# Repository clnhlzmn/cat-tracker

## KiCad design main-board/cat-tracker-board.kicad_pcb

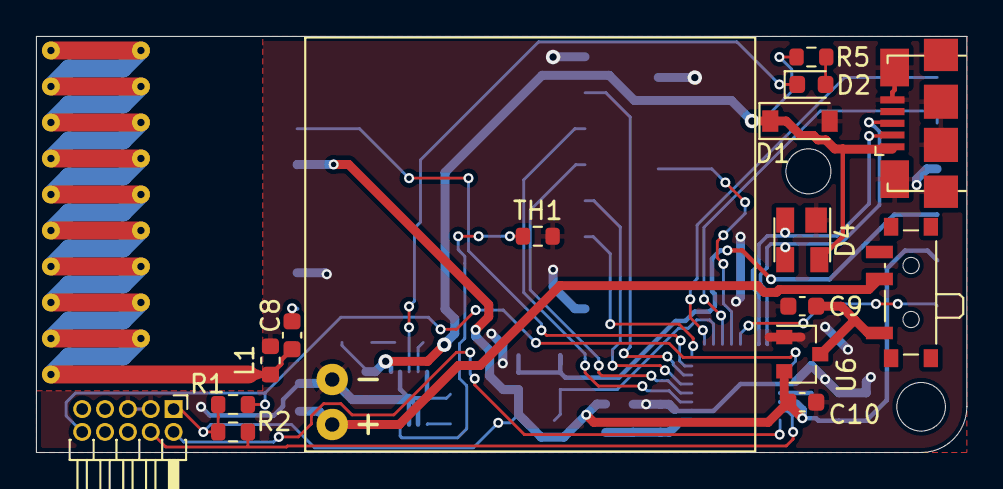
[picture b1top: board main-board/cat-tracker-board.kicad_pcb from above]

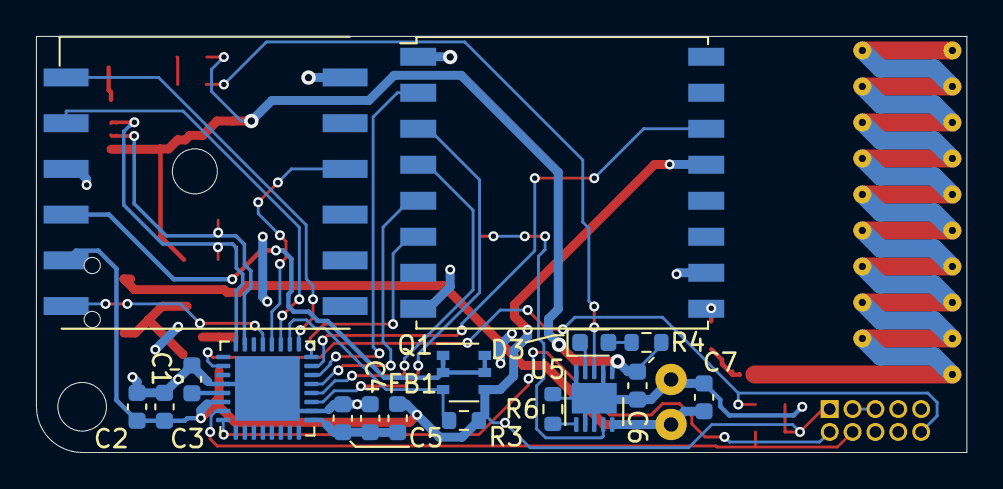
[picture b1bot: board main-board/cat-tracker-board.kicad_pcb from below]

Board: 2 copper layers, 51.7 x 23.1 mm, 34 parts (17 on the bottom side), 32 nets.

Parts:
AE1: Antenna; Texas_SWRA416_868MHz_915MHz
BT1: ASR00007; TinyCircuits_ASR00007
C1, C9, C10: 1 uF; C_0603_1608Metric
C2, C4: 10 uF; C_0603_1608Metric
C3, C5: 0.1 uF; C_0603_1608Metric
C6, C7: 4.7 uF; C_0603_1608Metric
C8: 1 pF; C_0603_1608Metric
D1: PTVS5V0S1UTR,115; D_SOD-123
D2, D3: LED; LED_0603_1608Metric
D4: PRTR5V0U2X; SOT-143
FB1: Ferrite_Bead; L_0603_1608Metric
J1: Conn_01x10; PinHeader_2x05_P1.27mm_Horizontal
J3: USB_B_Micro; USB_Micro-B_Amphenol_10118192_Horizontal
L1: 12 nH; L_0603_1608Metric
Q1: SI3443DDV-T1-GE3; TSOP-6_1.65x3.05mm_P0.95mm
R1, R2, R3: 100k; R_0603_1608Metric
R4, R5: 750; R_0603_1608Metric
R6: 14K; R_0603_1608Metric
SW1: PCM12SMTR; SW_SPDT_PCM12
TH1: 10K; R_0603_1608Metric
U1: ATSAMD21E18A-M; QFN-32-1EP_5x5mm_P0.5mm_EP3.6x3.6mm
U3: L80-R; Quectel_L80-R
U4: RFM95W-915S2; HOPERF_RFM9XW_SMD
U5: MCP73837/8-MF; DFN-10-1EP_3x3mm_P0.5mm_EP1.7x2.5mm
U6: MCP1700T-3602E/TT; SOT-23

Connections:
/GND: BT1.2 (-), C1.1, C2.2, C3.1, C4.2, C5.1, C6.2, C7.2, C9.2, C10.2, D1.2 (A2), D4.1 (GND), J1.3, J1.5, J3.5 (GND), J3.6 (Shield), L1.2, R6.2, TH1.2, U1.10 (GND), U1.28 (GND), U1.33 (EP), U3.3 (GND), U3.12 (GND), U4.1 (GND), U4.8 (GND), U4.10 (GND), U5.2 (VUSB), U5.5 (VSS), U5.7 (PROG2), U5.8 (~PG/~TE), U5.11 (VSS), U6.1 (GND)
/GPS_1PPS: U1.21 (PA22), U3.6 (1PPS)
/GPS_EN: Q1.3 (G), R3.2, U1.18 (PA17)
/GPS_RX: U1.19 (PA18), U3.2 (TXD1)
/GPS_TX: U1.17 (PA16), U3.1 (RXD1)
/GPS_nRESET: U1.20 (PA19), U3.10 (~RESET)
/MISO: U1.14 (PA11), U4.2 (MISO)
/MOSI: U1.11 (PA08), U4.3 (MOSI)
/NSS: U1.13 (PA10), U4.5 (NSS)
/RFM_INT: U1.15 (PA14), U4.14 (DIO0)
/RFM_RESET: U1.16 (PA15), U4.6 (RESET)
/SCK: U1.12 (PA09), U4.4 (SCK)
/SWCLK: J1.4, R2.2, U1.31 (PA30)
/SWDIO: J1.2, U1.32 (PA31)
/USBD+: D4.3 (I/O2), J3.3 (D+), U1.24 (PA25)
/USBD-: D4.2 (I/O1), J3.2 (D-), U1.23 (PA24)
/VBAT: BT1.1 (+), C7.1, SW1.2 (B), U5.10 (VBAT)
/VDD: C2.1, C3.2, C10.1, FB1.1, J1.1, Q1.4 (S), R1.1, R2.1, R3.1, U1.30 (VDDIN), U3.5 (V_BCKP), U4.13 (3.3V), U6.2 (VO)
/VUSB: C6.1, D1.1 (A1), D4.4 (VCC), J3.1 (VBUS), R4.2, R5.2, U5.1 (VAC)
/nRESET: J1.10, R1.2, U1.26 (~RESET)
unnamed: AE1.1 (A), C8.2, L1.1
unnamed: C1.2, U1.29 (VDDCORE)
unnamed: C4.1, C5.2, FB1.2, U1.9 (VDDANA)
unnamed: C9.1, SW1.1 (A), U6.3 (VI)
unnamed: D2.1 (K), U5.3 (STAT1)
unnamed: D2.2 (A), R5.1
unnamed: D3.1 (K), U5.4 (STAT2)
unnamed: D3.2 (A), R4.1
unnamed: Q1.1 (D), Q1.2 (D), Q1.5 (D), Q1.6 (D), U3.4 (VCC)
unnamed: R6.1, U5.6 (PROG1)
unnamed: TH1.1, U5.9 (THERM)
unnamed: C8.1, U4.9 (ANT)

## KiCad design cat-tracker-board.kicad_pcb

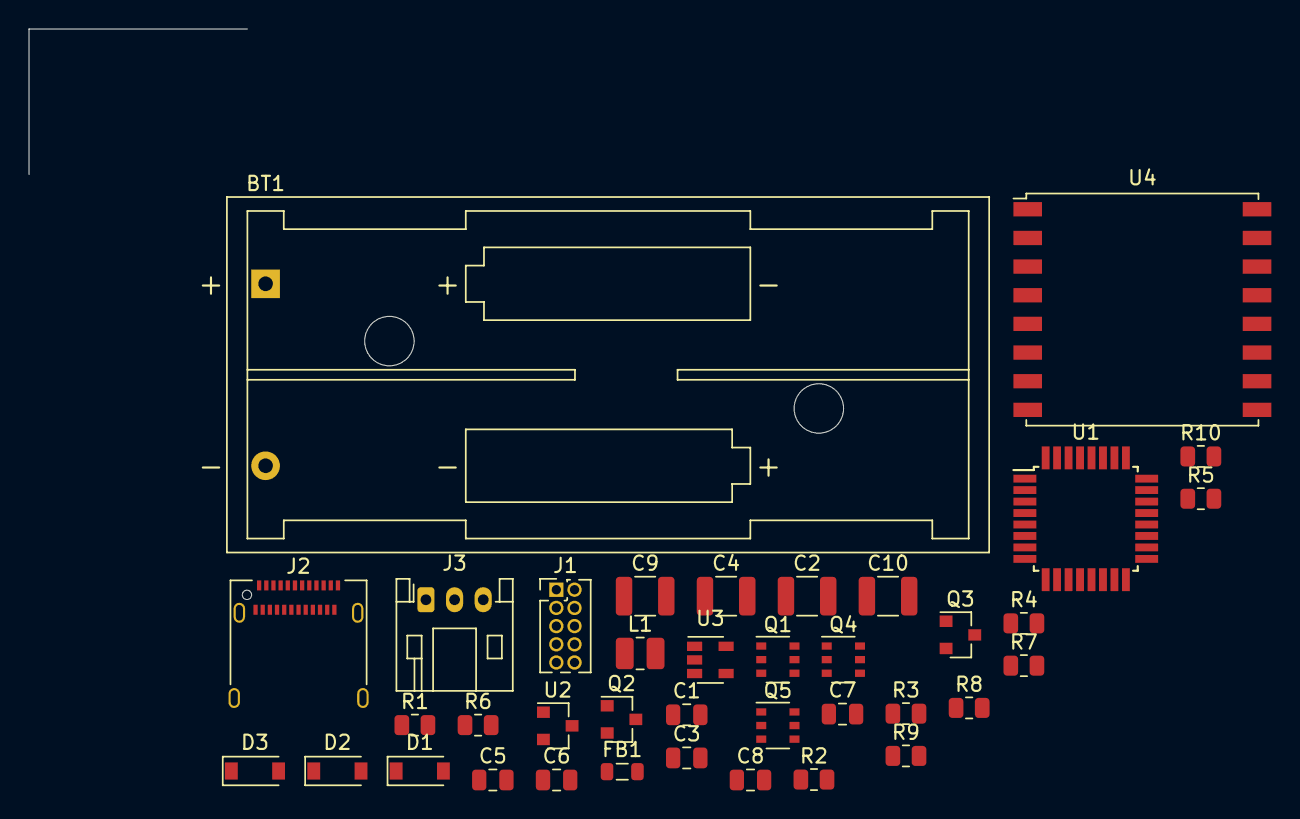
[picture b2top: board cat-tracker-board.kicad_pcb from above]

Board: 2 copper layers, 38 parts (0 on the bottom side), 30 nets, no tracks yet.

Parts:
BT1: Battery; BatteryHolder_Keystone_2468_2xAAA
C1: 1 uF; C_0805_2012Metric
C2, C4, C9, C10: 10 uF; C_1210_3225Metric
C3, C5, C6, C7, C8: 0.1 uF; C_0805_2012Metric
D1, D2: D; D_SOD-123
D3: D_Schottky; D_SOD-123
FB1: Ferrite_Bead; L_0805_2012Metric
J1: Conn_01x10; PinHeader_2x05_P1.27mm_Vertical
J2: USB_C_Receptacle_USB2.0; USB_C_Receptacle_Amphenol_12401610E4-2A
J3: Conn_01x03; JST_PH_S3B-PH-K_1x03_P2.00mm_Horizontal
L1: 4.7 uH; L_1008_2520Metric
Q1, Q4, Q5: SI3443DDV-T1-GE3; TSOP-6_1.65x3.05mm_P0.95mm
Q2: Q_PNP_BCE; SOT-23
Q3: Q_NPN_BCE; SOT-23
R1, R2, R3, R5, R8: 100k; R_0805_2012Metric
R4: 270k; R_0805_2012Metric
R6, R7: 500k; R_0805_2012Metric
R9, R10: 5.1k; R_0805_2012Metric
U1: ATSAMD21E18A-A; TQFP-32_7x7mm_P0.8mm
U2: LM3480-3.3; SOT-23
U3: TPS61097A-33DBVR; SOT-23-5
U4: RFM95W-915S2; HOPERF_RFM9XW_SMD

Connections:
/+3V3: C2.1, C3.2, C8.2, C10.2, D3.2, FB1.1, J1.1, Q5.4, R1.1, R2.1, R8.2, U1.30, U2.1, U3.4, U4.13
/GND: BT1.2, C1.1, C2.2, C3.1, C4.2, C5.1, C7.1, C8.1, C9.1, C10.1, J1.3, J1.5, J2.A1, J2.A12, J2.B1, J2.B12, J2.S1, J3.2, Q3.2, R3.2, R5.2, R9.2, R10.2, U1.10, U1.28, U2.3, U3.2, U4.1, U4.8, U4.10
/GPS_EN: Q5.3, R8.1, U1.18
/GPS_PWR: J3.3, Q5.1, Q5.2, Q5.5, Q5.6
/GPS_TX: J3.1, U1.17
/MISO: U1.14, U4.2
/MOSI: U1.11, U4.3
/NSS: U1.13, U4.5
/RFM_INT: U1.3, U4.14
/RFM_RESET: U1.4, U4.6
/SCK: U1.12, U4.4
/SWCLK: J1.4, R2.2, U1.31
/SWDIO: J1.2, U1.32
/USBDM: J2.A7, J2.B7, U1.23
/USBDP: J2.A6, J2.B6, U1.24
/VBAT: BT1.1, Q1.4
/VBAT_LVP: C9.2, L1.2, Q4.1, Q4.2, Q4.5, Q4.6, U3.1, U3.3
/VBAT_SW: C6.2, D1.2, Q1.1, Q1.2, Q1.5, Q1.6, Q4.4, R6.1, R7.1
/VUSB: C7.2, D3.1, J2.A4, J2.A9, J2.B4, J2.B9, Q1.3, R3.1, U2.2
/nRESET: J1.10, R1.2, U1.26
unnamed: C1.2, U1.29
unnamed: C4.1, C5.2, FB1.2, U1.9
unnamed: C6.1, D2.1, R4.1
unnamed: D1.1, D2.2
unnamed: J2.A5, R9.1
unnamed: J2.B5, R10.1
unnamed: L1.1, U3.5
unnamed: Q2.1, Q3.3, Q4.3, R7.2
unnamed: Q2.2, R6.2
unnamed: Q2.3, Q3.1, R4.2, R5.1

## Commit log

2021-04-23 Added new kicad project.
2021-04-29 Added RFM95 module.
2021-04-29 Added MCU and friends and connected to radio.
2021-05-01 Changed mcu to 32 pin, added usb, power.
2021-05-01 Added some part numbers, updated boost regulator to a part that's not obsolete.
2021-05-01 Added low voltage cutoff circuit for batteries.
2021-05-02 Added GPS connector and switch, annotated symbols, and assigned footprints.
2021-05-02 Fixed BJT pin numbers.
2021-05-02 Updated PCB with footprints.
2021-05-02 Added cat-tracker-board.pretty for board specific footprints.
2021-05-02 Updated pcb with new BJT nets.
2021-05-02 Moved main board to sub folder.
2021-05-02 Added battery board schematic and layout.
2021-05-02 Updated battery-board gitignore.
2021-05-02 Added battery-board footprint in main-board lib.
2021-05-02 Updated main board layout with battery board footprint.
2021-05-02 Added right angle SMA connector.
2021-05-02 Added lora antenna connector.
2021-05-02 Added aux bom with antenna PN.
2021-05-02 Assigned remaining main-board part numbers.
2021-05-02 Updated main board pcb.
2021-05-02 Changed programming header to right angle and updated pcb.
2021-05-02 Placed all parts on board.
2021-05-02 Added zip tie slots.
2021-05-02 Rescued ferrite bead symbol.
2021-05-02 Started routing.
2021-05-02 Finished layout.
2021-05-02 Rescued ferrite bead (again?).
2021-05-02 Updated battery board pns and added aux bom.
2021-05-02 Added fasteners to main board aux bom.
2021-05-02 Added CPH logo.
2021-05-02 Updated plot settings.
2021-05-02 Updated battery board plot settings.
2021-05-03 Added version number to boards.
2021-05-29 Remove LVP circuit and usb/bat selector switch, add slide switch for bat, change switch ind to 10uH.
2021-05-30 Improve boost converter layout, change version to 0.1.0.
2021-05-30 Change boost converter inductor to the one used in the reference design.
2021-05-31 Remove boost converter, replace with low Vf schottky.
2021-07-03 Remove battery board.
2021-07-04 Add A5135-H.
2021-07-05 Add L80 GPS, charge ic, and battery protection ic.
2021-07-05 Add charger support components.
2021-07-05 Add support components for battery protection.
2021-07-06 Rescue symbols.
2021-07-06 Add MCP 1700 3.6V regulator.
2021-07-06 Annotate, assign footprints, and assign part numbers.
2021-07-07 Change usb to micro B type.
2021-07-07 Change passives to 0603, change mcu to qfp, change battery to asr00007.
2021-07-08 Add antenna, change USB to smd, add gps switch, connect gps.
2021-07-08 Rescue MCU symbol.
2021-07-08 Arrange all parts within board edge.
2021-07-09 Rearrange parts.
2021-07-09 Change differential pair settings back to default.
2021-07-09 Add some tracks.
2021-07-10 Change switch connection to improve layout.
2021-07-15 Work on layout.
2021-07-16 Correct footprint assignment for U5 and work on layout.
2021-07-18 Route almost everything.
2022-01-17 Update to KiCad v6
2022-01-17 Add antenna matching, update some PNs
2022-01-17 Clean up silk
2022-01-17 Remove unused items from aux bom
2022-01-18 Add alternate for GPS
2022-01-18 Start changing to MCP73838
2022-01-19 Finish layout for new charger
2022-01-20 Fixed charger symbol
2022-01-20 Update bom
